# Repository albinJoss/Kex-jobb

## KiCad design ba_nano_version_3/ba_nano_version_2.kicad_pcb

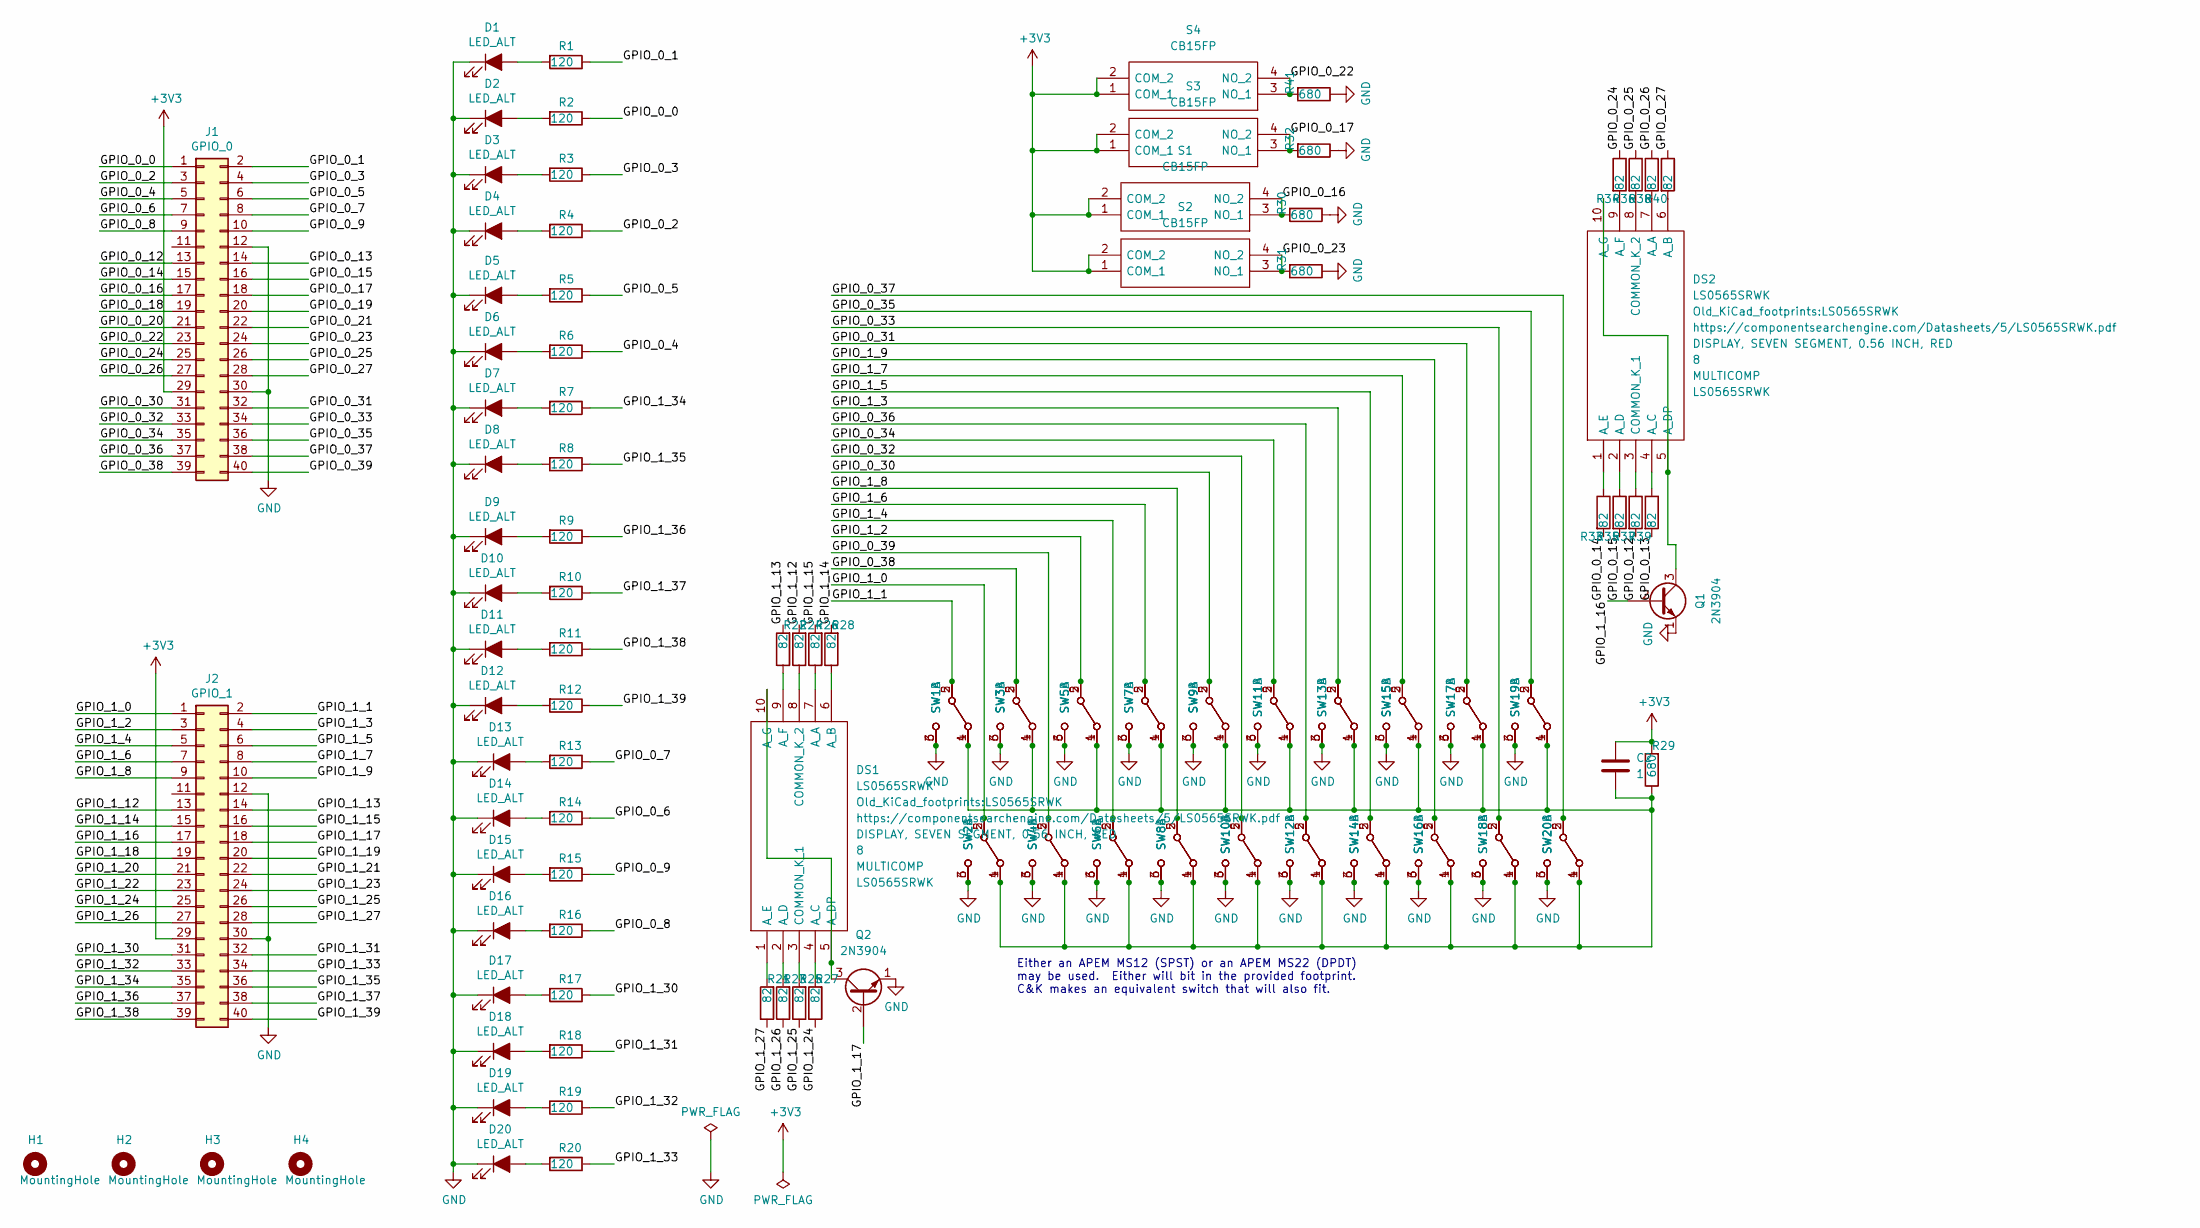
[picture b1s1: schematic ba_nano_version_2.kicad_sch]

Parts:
C2: 1; C_2220_5650Metric
D1, D2, D3, D4, D5, D6, D7, D8, D9, D10, D11, D12, D13, D14, D15, D16, D17, D18, D19, D20: LED_ALT; LED_1210_3225Metric_Castelled
DS1, DS2: LS0565SRWK; Manufacturer_Part_Number LS0565SRWK
H1, H2, H3, H4: MountingHole; MountingHole_3.2mm_M3_Pad
J1: GPIO_0; PinHeader_2x20_P2.54mm_Vertical
J2: GPIO_1; PinHeader_2x20_P2.54mm_Vertical
Q1, Q2: 2N3904; TO-92_Inline
R1, R2, R3, R4, R5, R6, R7, R8, R9, R10, R11, R12, R13, R14, R15, R16, R17, R18, R19, R20: 120; R_0805_2012Metric_Pad1.20x1.40mm_HandSolder
R21, R22, R23, R24, R25, R26, R27, R28, R33, R34, R35, R36, R37, R38, R39, R40: 82; R_1206_3216Metric
R29, R30, R31, R32, R41: 680; R_1206_3216Metric
S1, S2, S3, S4: CB15FP; Manufacturer_Part_Number CB15FP; Mouser Part Number 633-CB15FP
SW1, SW2, SW3, SW4, SW5, SW6, SW7, SW8, SW9, SW10, SW11, SW12, SW13, SW14, SW15, SW16, SW17, SW18, SW19, SW20: DPDT-3.2MM

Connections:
+3V3: C2.1, J1.29, J2.29, R29.2, S1.1 (COM_1), S1.2 (COM_2), S2.1 (COM_1), S2.2 (COM_2), S3.1 (COM_1), S3.2 (COM_2), S4.1 (COM_1), S4.2 (COM_2)
/GPIO_0_0: J1.1, R2.1
/GPIO_0_1: J1.2, R1.1
/GPIO_0_2: J1.3, R4.1
/GPIO_0_3: J1.4, R3.1
/GPIO_0_4: J1.5, R6.1
/GPIO_0_5: J1.6, R5.1
/GPIO_0_6: J1.7, R14.1
/GPIO_0_7: J1.8, R13.1
/GPIO_0_8: J1.9, R16.1
/GPIO_0_9: J1.10, R15.1
/GPIO_0_12: J1.13, R37.2
/GPIO_0_13: J1.14, R39.2
/GPIO_0_14: J1.15, R33.2
/GPIO_0_15: J1.16, R35.2
/GPIO_0_16: J1.17, R30.2, S1.3 (NO_1), S1.4 (NO_2)
/GPIO_0_17: J1.18, R32.2, S3.3 (NO_1), S3.4 (NO_2)
/GPIO_0_18: J1.19
/GPIO_0_19: J1.20
/GPIO_0_20: J1.21
/GPIO_0_21: J1.22
/GPIO_0_22: J1.23, R41.2, S4.3 (NO_1), S4.4 (NO_2)
/GPIO_0_23: J1.24, R31.2, S2.3 (NO_1), S2.4 (NO_2)
/GPIO_0_24: J1.25, R34.1
/GPIO_0_25: J1.26, R36.1
/GPIO_0_26: J1.27, R38.1
/GPIO_0_27: J1.28, R40.1
/GPIO_0_30: J1.31, SW9.2 (B), SW9.5 (B)
/GPIO_0_31: J1.32, SW17.2 (B), SW17.5 (B)
/GPIO_0_32: J1.33, SW10.2 (B), SW10.5 (B)
/GPIO_0_33: J1.34, SW18.2 (B), SW18.5 (B)
/GPIO_0_34: J1.35, SW11.2 (B), SW11.5 (B)
/GPIO_0_35: J1.36, SW19.2 (B), SW19.5 (B)
/GPIO_0_36: J1.37, SW12.2 (B), SW12.5 (B)
/GPIO_0_37: J1.38, SW20.2 (B), SW20.5 (B)
/GPIO_0_38: J1.39, SW3.2 (B), SW3.5 (B)
/GPIO_0_39: J1.40, SW4.2 (B), SW4.5 (B)
/GPIO_1_0: J2.1, SW2.2 (B), SW2.5 (B)
/GPIO_1_1: J2.2, SW1.2 (B), SW1.5 (B)
/GPIO_1_2: J2.3, SW5.2 (B), SW5.5 (B)
/GPIO_1_3: J2.4, SW13.2 (B), SW13.5 (B)
/GPIO_1_4: J2.5, SW6.2 (B), SW6.5 (B)
/GPIO_1_5: J2.6, SW14.2 (B), SW14.5 (B)
/GPIO_1_6: J2.7, SW7.2 (B), SW7.5 (B)
/GPIO_1_7: J2.8, SW15.2 (B), SW15.5 (B)
/GPIO_1_8: J2.9, SW8.2 (B), SW8.5 (B)
/GPIO_1_9: J2.10, SW16.2 (B), SW16.5 (B)
/GPIO_1_12: J2.13, R24.2
/GPIO_1_13: J2.14, R22.2
/GPIO_1_14: J2.15, R28.2
/GPIO_1_15: J2.16, R26.2
/GPIO_1_16: J2.17, Q1.2 (B)
/GPIO_1_17: J2.18, Q2.2 (B)
/GPIO_1_18: J2.19
/GPIO_1_19: J2.20
/GPIO_1_20: J2.21
/GPIO_1_21: J2.22
/GPIO_1_22: J2.23
/GPIO_1_23: J2.24
/GPIO_1_24: J2.25, R27.1
/GPIO_1_25: J2.26, R25.1
/GPIO_1_26: J2.27, R23.1
/GPIO_1_27: J2.28, R21.1
/GPIO_1_30: J2.31, R17.1
/GPIO_1_31: J2.32, R18.1
/GPIO_1_32: J2.33, R19.1
/GPIO_1_33: J2.34, R20.1
/GPIO_1_34: J2.35, R7.1
/GPIO_1_35: J2.36, R8.1
/GPIO_1_36: J2.37, R9.1
/GPIO_1_37: J2.38, R10.1
/GPIO_1_38: J2.39, R11.1
/GPIO_1_39: J2.40, R12.1
GND: D1.1 (K), D2.1 (K), D3.1 (K), D4.1 (K), D5.1 (K), D6.1 (K), D7.1 (K), D8.1 (K), D9.1 (K), D10.1 (K), D11.1 (K), D12.1 (K), D13.1 (K), D14.1 (K), D15.1 (K), D16.1 (K), D17.1 (K), D18.1 (K), D19.1 (K), D20.1 (K), J1.12, J1.30, J2.12, J2.30, Q1.1 (E), Q2.1 (E), R30.1, R31.1, R32.1, R41.1, SW1.3 (C), SW1.6 (C), SW2.3 (C), SW2.6 (C), SW3.3 (C), SW3.6 (C), SW4.3 (C), SW4.6 (C), SW5.3 (C), SW5.6 (C), SW6.3 (C), SW6.6 (C), SW7.3 (C), SW7.6 (C), SW8.3 (C), SW8.6 (C), SW9.3 (C), SW9.6 (C), SW10.3 (C), SW10.6 (C), SW11.3 (C), SW11.6 (C), SW12.3 (C), SW12.6 (C), SW13.3 (C), SW13.6 (C), SW14.3 (C), SW14.6 (C), SW15.3 (C), SW15.6 (C), SW16.3 (C), SW16.6 (C), SW17.3 (C), SW17.6 (C), SW18.3 (C), SW18.6 (C), SW19.3 (C), SW19.6 (C), SW20.3 (C), SW20.6 (C)
unnamed: C2.2, R29.1, SW1.1 (A), SW1.4 (A), SW2.1 (A), SW2.4 (A), SW3.1 (A), SW3.4 (A), SW4.1 (A), SW4.4 (A), SW5.1 (A), SW5.4 (A), SW6.1 (A), SW6.4 (A), SW7.1 (A), SW7.4 (A), SW8.1 (A), SW8.4 (A), SW9.1 (A), SW9.4 (A), SW10.1 (A), SW10.4 (A), SW11.1 (A), SW11.4 (A), SW12.1 (A), SW12.4 (A), SW13.1 (A), SW13.4 (A), SW14.1 (A), SW14.4 (A), SW15.1 (A), SW15.4 (A), SW16.1 (A), SW16.4 (A), SW17.1 (A), SW17.4 (A), SW18.1 (A), SW18.4 (A), SW19.1 (A), SW19.4 (A), SW20.1 (A), SW20.4 (A)
unnamed: D1.2 (A), R1.2
unnamed: D2.2 (A), R2.2
unnamed: D3.2 (A), R3.2
unnamed: D4.2 (A), R4.2
unnamed: D5.2 (A), R5.2
unnamed: D6.2 (A), R6.2
unnamed: D7.2 (A), R7.2
unnamed: D8.2 (A), R8.2
unnamed: D9.2 (A), R9.2
unnamed: D10.2 (A), R10.2
unnamed: D11.2 (A), R11.2
unnamed: D12.2 (A), R12.2
unnamed: D13.2 (A), R13.2
unnamed: D14.2 (A), R14.2
unnamed: D15.2 (A), R15.2
unnamed: D16.2 (A), R16.2
unnamed: D17.2 (A), R17.2
unnamed: D18.2 (A), R18.2
unnamed: D19.2 (A), R19.2
unnamed: D20.2 (A), R20.2
unnamed: DS1.1 (A_E), R21.2
unnamed: DS1.2 (A_D), R23.2
unnamed: DS1.3 (COMMON_K_1), R25.2
unnamed: DS1.4 (A_C), R27.2
unnamed: DS1.6 (A_B), R28.1
unnamed: DS1.7 (A_A), R26.1
unnamed: DS1.8 (COMMON_K_2), R24.1
unnamed: DS1.9 (A_F), R22.1
unnamed: DS1.5 (A_DP), DS1.10 (A_G), Q2.3 (C)
unnamed: DS2.1 (A_E), R33.1
unnamed: DS2.2 (A_D), R35.1
unnamed: DS2.3 (COMMON_K_1), R37.1
unnamed: DS2.4 (A_C), R39.1
unnamed: DS2.6 (A_B), R40.2
unnamed: DS2.7 (A_A), R38.2
unnamed: DS2.8 (COMMON_K_2), R36.2
unnamed: DS2.9 (A_F), R34.2
unnamed: DS2.5 (A_DP), DS2.10 (A_G), Q1.3 (C)

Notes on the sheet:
Either an APEM MS12 (SPST) or an APEM MS22 (DPDT) may be used. Either will bit in the provided footprint. C&K makes an equivalent switch that will also fit.

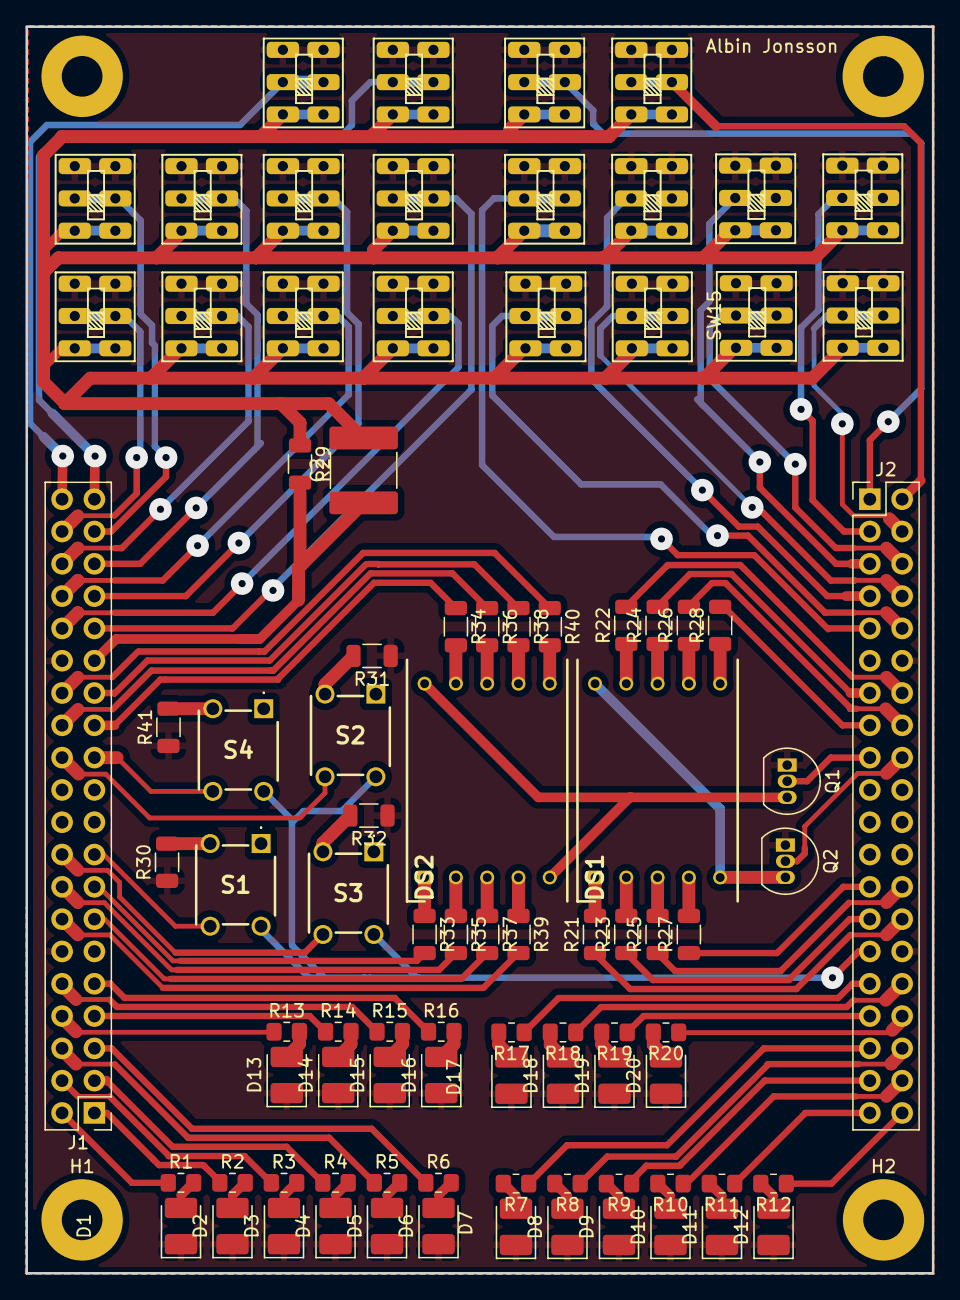
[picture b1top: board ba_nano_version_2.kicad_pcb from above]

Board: 2 copper layers, 71.3 x 98.0 mm, 96 parts (0 on the bottom side), 103 nets.

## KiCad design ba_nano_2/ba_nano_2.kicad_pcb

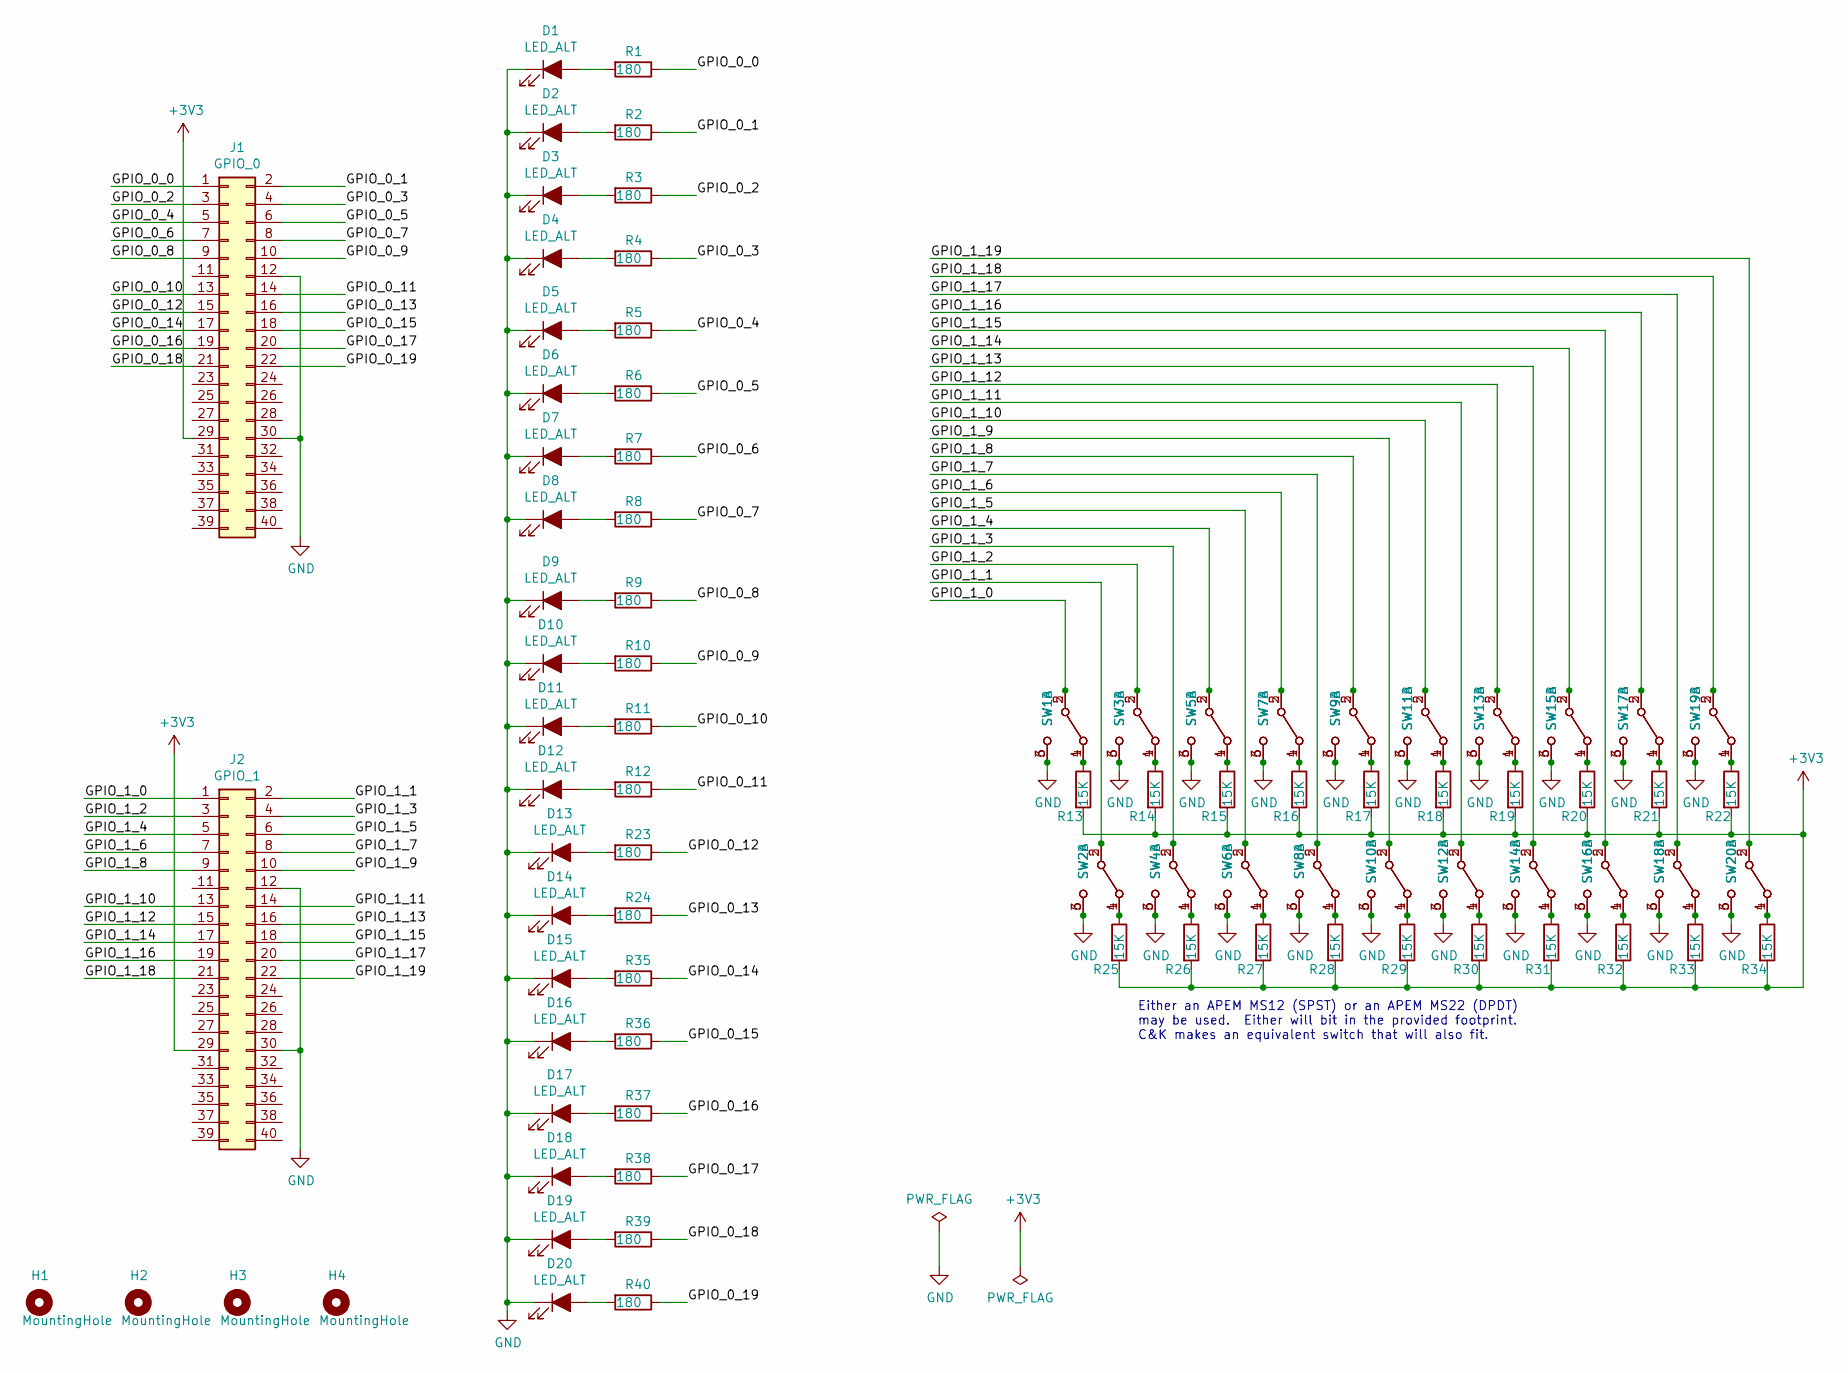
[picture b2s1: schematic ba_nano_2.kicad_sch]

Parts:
D1, D2, D3, D4, D5, D6, D7, D8, D9, D10, D11, D12, D13, D14, D15, D16, D17, D18, D19, D20: LED_ALT; LED_1210_3225Metric_Castellated
H1, H2, H3, H4: MountingHole; MountingHole_3.2mm_M3_Pad
J1: GPIO_0; PinHeader_2x20_P2.54mm_Vertical
J2: GPIO_1; PinHeader_2x20_P2.54mm_Vertical
R1, R2, R3, R4, R5, R6, R7, R8, R9, R10, R11, R12, R23, R24, R35, R36, R37, R38, R39, R40: 180; R_0603_1608Metric_Pad1.05x0.95mm_HandSolder
R13, R14, R15, R16, R17, R18, R19, R20, R21, R22, R25, R26, R27, R28, R29, R30, R31, R32, R33, R34: 15K; R_0603_1608Metric_Pad1.05x0.95mm_HandSolder
SW1, SW2, SW3, SW4, SW5, SW6, SW7, SW8, SW9, SW10, SW11, SW12, SW13, SW14, SW15, SW16, SW17, SW18, SW19, SW20: DPDT-3.2MM

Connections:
+3V3: J1.29, J2.29, R13.2, R14.2, R15.2, R16.2, R17.2, R18.2, R19.2, R20.2, R21.2, R22.2, R25.2, R26.2, R27.2, R28.2, R29.2, R30.2, R31.2, R32.2, R33.2, R34.2
/GPIO_0_0: J1.1, R1.1
/GPIO_0_1: J1.2, R2.1
/GPIO_0_2: J1.3, R3.1
/GPIO_0_3: J1.4, R4.1
/GPIO_0_4: J1.5, R5.1
/GPIO_0_5: J1.6, R6.1
/GPIO_0_6: J1.7, R7.1
/GPIO_0_7: J1.8, R8.1
/GPIO_0_8: J1.9, R9.1
/GPIO_0_9: J1.10, R10.1
/GPIO_0_10: J1.13, R11.1
/GPIO_0_11: J1.14, R12.1
/GPIO_0_12: J1.15, R23.1
/GPIO_0_13: J1.16, R24.1
/GPIO_0_14: J1.17, R35.1
/GPIO_0_15: J1.18, R36.1
/GPIO_0_16: J1.19, R37.1
/GPIO_0_17: J1.20, R38.1
/GPIO_0_18: J1.21, R39.1
/GPIO_0_19: J1.22, R40.1
/GPIO_1_0: J2.1, SW1.2 (B), SW1.5 (B)
/GPIO_1_1: J2.2, SW2.2 (B), SW2.5 (B)
/GPIO_1_2: J2.3, SW3.2 (B), SW3.5 (B)
/GPIO_1_3: J2.4, SW4.2 (B), SW4.5 (B)
/GPIO_1_4: J2.5, SW5.2 (B), SW5.5 (B)
/GPIO_1_5: J2.6, SW6.2 (B), SW6.5 (B)
/GPIO_1_6: J2.7, SW7.2 (B), SW7.5 (B)
/GPIO_1_7: J2.8, SW8.2 (B), SW8.5 (B)
/GPIO_1_8: J2.9, SW9.2 (B), SW9.5 (B)
/GPIO_1_9: J2.10, SW10.2 (B), SW10.5 (B)
/GPIO_1_10: J2.13, SW11.2 (B), SW11.5 (B)
/GPIO_1_11: J2.14, SW12.2 (B), SW12.5 (B)
/GPIO_1_12: J2.15, SW13.2 (B), SW13.5 (B)
/GPIO_1_13: J2.16, SW14.2 (B), SW14.5 (B)
/GPIO_1_14: J2.17, SW15.2 (B), SW15.5 (B)
/GPIO_1_15: J2.18, SW16.2 (B), SW16.5 (B)
/GPIO_1_16: J2.19, SW17.2 (B), SW17.5 (B)
/GPIO_1_17: J2.20, SW18.2 (B), SW18.5 (B)
/GPIO_1_18: J2.21, SW19.2 (B), SW19.5 (B)
/GPIO_1_19: J2.22, SW20.2 (B), SW20.5 (B)
GND: D1.1 (K), D2.1 (K), D3.1 (K), D4.1 (K), D5.1 (K), D6.1 (K), D7.1 (K), D8.1 (K), D9.1 (K), D10.1 (K), D11.1 (K), D12.1 (K), D13.1 (K), D14.1 (K), D15.1 (K), D16.1 (K), D17.1 (K), D18.1 (K), D19.1 (K), D20.1 (K), J1.12, J1.30, J2.12, J2.30, SW1.3 (C), SW1.6 (C), SW2.3 (C), SW2.6 (C), SW3.3 (C), SW3.6 (C), SW4.3 (C), SW4.6 (C), SW5.3 (C), SW5.6 (C), SW6.3 (C), SW6.6 (C), SW7.3 (C), SW7.6 (C), SW8.3 (C), SW8.6 (C), SW9.3 (C), SW9.6 (C), SW10.3 (C), SW10.6 (C), SW11.3 (C), SW11.6 (C), SW12.3 (C), SW12.6 (C), SW13.3 (C), SW13.6 (C), SW14.3 (C), SW14.6 (C), SW15.3 (C), SW15.6 (C), SW16.3 (C), SW16.6 (C), SW17.3 (C), SW17.6 (C), SW18.3 (C), SW18.6 (C), SW19.3 (C), SW19.6 (C), SW20.3 (C), SW20.6 (C)
unnamed: D1.2 (A), R1.2
unnamed: D2.2 (A), R2.2
unnamed: D3.2 (A), R3.2
unnamed: D4.2 (A), R4.2
unnamed: D5.2 (A), R5.2
unnamed: D6.2 (A), R6.2
unnamed: D7.2 (A), R7.2
unnamed: D8.2 (A), R8.2
unnamed: D9.2 (A), R9.2
unnamed: D10.2 (A), R10.2
unnamed: D11.2 (A), R11.2
unnamed: D12.2 (A), R12.2
unnamed: D13.2 (A), R23.2
unnamed: D14.2 (A), R24.2
unnamed: D15.2 (A), R35.2
unnamed: D16.2 (A), R36.2
unnamed: D17.2 (A), R37.2
unnamed: D18.2 (A), R38.2
unnamed: D19.2 (A), R39.2
unnamed: D20.2 (A), R40.2
unnamed: R13.1, SW1.1 (A), SW1.4 (A)
unnamed: R14.1, SW3.1 (A), SW3.4 (A)
unnamed: R15.1, SW5.1 (A), SW5.4 (A)
unnamed: R16.1, SW7.1 (A), SW7.4 (A)
unnamed: R17.1, SW9.1 (A), SW9.4 (A)
unnamed: R18.1, SW11.1 (A), SW11.4 (A)
unnamed: R19.1, SW13.1 (A), SW13.4 (A)
unnamed: R20.1, SW15.1 (A), SW15.4 (A)
unnamed: R21.1, SW17.1 (A), SW17.4 (A)
unnamed: R22.1, SW19.1 (A), SW19.4 (A)
unnamed: R25.1, SW2.1 (A), SW2.4 (A)
unnamed: R26.1, SW4.1 (A), SW4.4 (A)
unnamed: R27.1, SW6.1 (A), SW6.4 (A)
unnamed: R28.1, SW8.1 (A), SW8.4 (A)
unnamed: R29.1, SW10.1 (A), SW10.4 (A)
unnamed: R30.1, SW12.1 (A), SW12.4 (A)
unnamed: R31.1, SW14.1 (A), SW14.4 (A)
unnamed: R32.1, SW16.1 (A), SW16.4 (A)
unnamed: R33.1, SW18.1 (A), SW18.4 (A)
unnamed: R34.1, SW20.1 (A), SW20.4 (A)

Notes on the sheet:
Either an APEM MS12 (SPST) or an APEM MS22 (DPDT) may be used. Either will bit in the provided footprint. C&K makes an equivalent switch that will also fit.

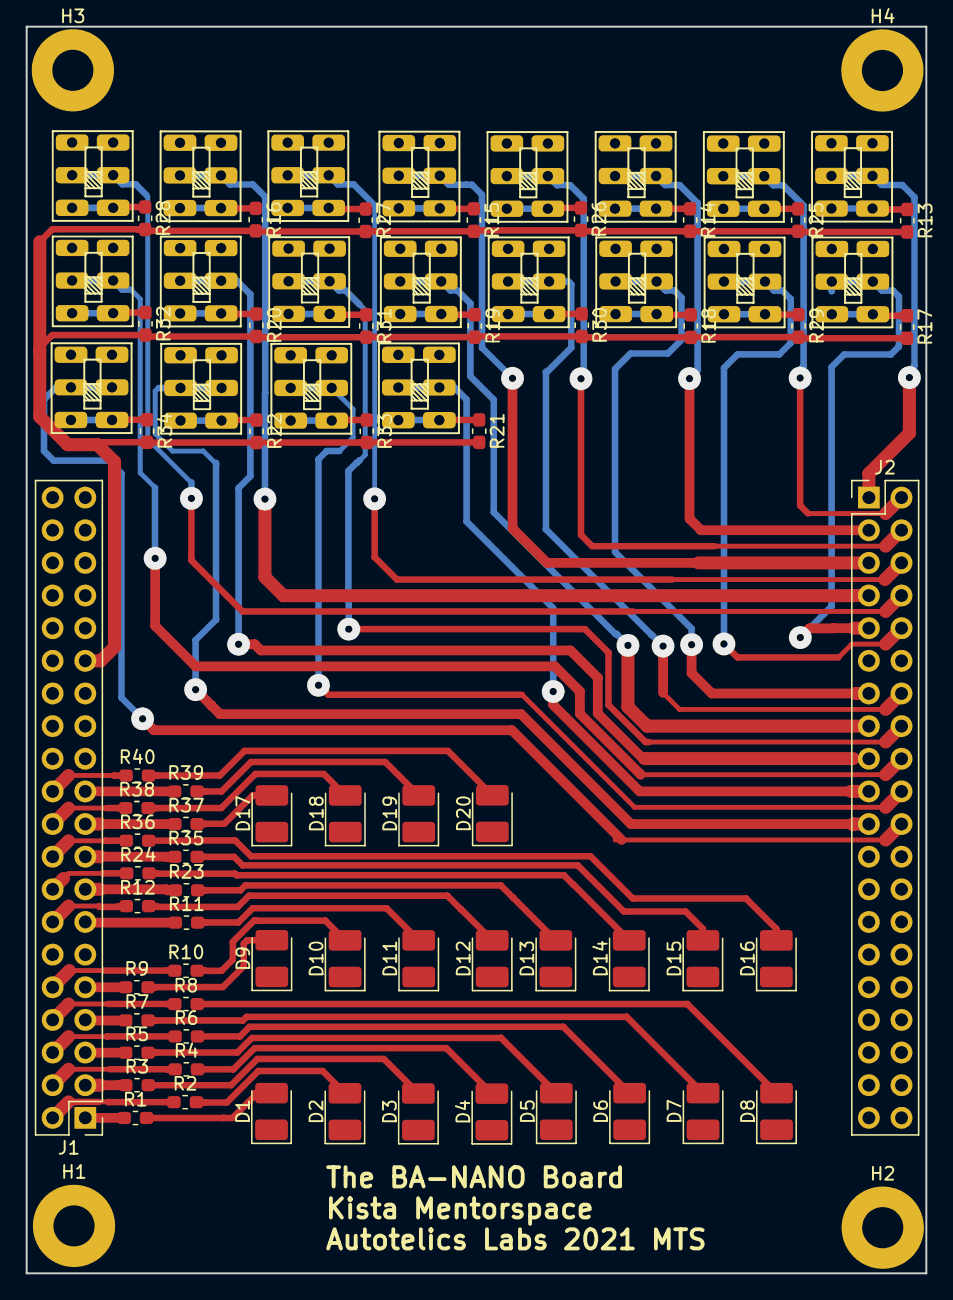
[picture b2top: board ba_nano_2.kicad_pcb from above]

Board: 2 copper layers, 70.0 x 97.0 mm, 86 parts (0 on the bottom side), 82 nets.

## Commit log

2022-05-02 Added testing quartus progam
2022-05-03 Made changes to KiCad schematic and CAD drawing. Changed SSDs and buttons
2022-05-04 Completed the adding of buttons and two independetely controlled SSDs
